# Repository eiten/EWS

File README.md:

# 🔌 Universal Voron Power & CAN HAT (EWS)

> 🌍 **Languages:** [English](README.md) | [Deutsch](README.de.md)

A universal interface board (HAT) for Raspberry Pi 4/5 and Radxa Rock 5B designed for use in Voron 3D printers. Provides powerful 5V supply (8A), CAN-Bus interface (USB-Bridge or Native), and USB hub.

## 📚 Contents

<!-- @import "[TOC]" {cmd="toc" depthFrom=1 depthTo=6 orderedList=false} -->

<!-- code_chunk_output -->

- [🔌 Universal Voron Power & CAN HAT (EWS)](#-universal-voron-power--can-hat-ews)
  - [📚 Contents](#-contents)
  - [🎯 About EWS](#-about-ews)
  - [🚨 Problems Addressed](#-problems-addressed)
  - [✨ Features](#-features)
    - [🔋 Power Supply (24V Input)](#-power-supply-24v-input)
    - [⚡ DC/DC Converter (5V Output)](#-dcdc-converter-5v-output)
    - [🔌 Logic Power Supply (Power Path)](#-logic-power-supply-power-path)
    - [💻 MCU & CAN Interface](#-mcu--can-interface)
    - [📡 USB Hub](#-usb-hub)
  - [📋 Klipper Configuration](#-klipper-configuration)
    - [Basic MCU Setup](#basic-mcu-setup)
  - [🔌 Pinout & Connector Assignment](#-pinout--connector-assignment)
    - [Power Input](#power-input)
    - [CAN-Bus Ports](#can-bus-ports)
    - [USB Ports](#usb-ports)
  - [🛠️ PCB Specifications](#️-pcb-specifications)
  - [⚠️ Manufacturing Recommendations](#️-manufacturing-recommendations)
    - [PCB Manufacturing](#pcb-manufacturing)
    - [Assembly Notes](#assembly-notes)
    - [Component Sourcing](#component-sourcing)
  - [🛠️ Technical Specifications](#️-technical-specifications)
  - [📚 Additional Resources](#-additional-resources)
  - [📝 Changelog](#-changelog)
  - [License](#license)

<!-- /code_chunk_output -->

## 🎯 About EWS

**EWS** stands for "Eierlegende Wollmilchsau" (German for "egg-laying woolly milk pig") - a humorous term for a universal solution that does everything. This HAT lives up to its nickname by combining multiple essential functions for Voron 3D printer control systems in a single, compact board.

The board addresses common pain points in Voron builds by providing robust power distribution, reliable CAN communication, and convenient USB connectivity while maintaining compatibility with both Raspberry Pi and Radxa Rock 5B single-board computers.

## 🚨 Problems Addressed

This board was designed to solve multiple critical issues commonly encountered in high-performance 3D printer setups:

### ⚡ **Power & Supply Issues**
- **Unstable SBC power supply** - Many setups suffer from voltage drops and power instability
- **Separate power injection required** - USB-C touchscreens often need additional power supplies
- **Power distribution complexity** - Multiple power sources create wiring challenges

### 🔗 **CAN Communication Problems**
- **USB-CAN adapters** - Difficult to mount, unreliable connections, additional failure points
- **Controller board limitations** - Using Spider/Octopus as CAN bridge often has built-in termination resistors
- **CAN topology conflicts** - Can't run both CAN toolheads and ADXL boards simultaneously on many controller boards
- **Native CAN unavailable** - Most SBC setups lack proper native CAN interface utilization

### 🔥 **Safety Concerns**
- **Fire hazard from thermal runaway** - No way to disconnect toolhead power during emergencies
- **Uncontrolled power delivery** - Toolheads remain powered even during faults
- **Limited emergency shutdown** - Difficult to implement comprehensive safety cutoffs

### 🔌 **Wiring & Installation**
- **Complex cable management** - CAN and 24V power start from different locations
- **Multiple connection points** - Increases failure modes and installation complexity
- **Inadequate connector standards** - Mix of different connector types creates confusion

### 🖥️ **USB & Peripheral Issues**
- **Limited USB ports** - SBCs often lack sufficient high-power USB connectivity
- **USB hub limitations** - External hubs add complexity and potential points of failure
- **Power delivery standards** - Inconsistent USB-C power delivery for modern touchscreens

## ✨ Features

### 🔋 Power Supply (24V Input)

- **Input Voltage:** 24V DC nominal
- **Connectors:** XT30PW-F (horizontal) or 5.08mm screw terminal
- **Toolhead Switching:** 2x P-Channel MOSFETs (CJAC70P06, -60V, -70A, RDSon ~8mΩ) controlled by PB2 and PA5 for toolhead power switching (safety feature if PWM-FET on toolhead fails)
- **Overvoltage Protection:** TVS diode (SMAJ26A, 26V Standoff, Unidirectional) to GND
- **Input Protection:** Distributed fusing (5A for DC/DC, 5A each for CAN ports)

### ⚡ DC/DC Converter (5V Output)

- **Controller:** MaxLinear XR76208 (Synchronous Step-Down, 8A, COT)
- **Input Voltage:** 12-24V DC (enable circuit with Zener diode)
- **Input Fuse:** 5A SMD 1812 Slow Blow
- **Reverse Polarity Protection:** SS56 Schottky diode
- **Output Voltage:** 5.1V (set via feedback divider: R_Top=15kΩ, R_Bottom=2.0kΩ)
- **Switching Frequency:** ~600kHz (set via Ron=30kOhm)
- **Inductance:** 3.3µH Shielded (Sunlord MDA1050-3R3M, Isat ~17A)
- **Input Capacitors:** 4x 10µF 1206 ceramic + 1x 100µF electrolytic/polymer (bulk)
- **Output Capacitors:** 4x 22µF 1206 ceramic
- **Stability:** Feed-forward capacitor (Cff) 1nF parallel to upper feedback resistor
- **Soft-Start:** 100nF at SS pin (~6ms startup time)
- **Current Limit:** 5.1kΩ resistor (~10.2A limit)
- **Enable:** Zener diode-based circuit for 12-24V input voltage range

### 🔌 Logic Power Supply (Power Path)

- **Concept:** Separation of +5V_PWR (high current for screen/webcam) and +5V_LOGIC (for MCU/Hub)
- **Diode OR-ing:** 2x Schottky diodes (1N5819WS, 1A)
  - Source 1: USB_VBUS (from Pi/PC) → Diode → +5V_LOGIC
  - Source 2: +5V_BUCK (from 8A regulator) → Diode → +5V_LOGIC
- **Purpose:** Board is USB-flashable without 24V supply, no backflow to PC
- **3.3V Generation:** LDO (XC6206) powered from +5V_LOGIC

### 🧠 MCU & CAN Interface

- **Microcontroller:** STM32G0B1KBU6 (UFQFPN-32)
- **Clocking:** Crystal-less (Internal HSI48 with Clock Recovery System CRS via USB)
- **Pi Connection:**
  - USB (PA11/PA12) to USB Hub
  - UART (PA9/PA10) to Pi Header (Pin 8/10) via jumperable connection
  - NRST to Pi GPIO 22 (via 1kΩ) + button to GND + 100nF cap
  - BOOT0 (Pin 24/PA14 shared with SWCLK) to Pi GPIO 27 (via 1kΩ) + button to 3.3V + 10kΩ pull-down
- **CAN Transceiver:** MCP2542WFD (or compatible)
- **Muxing:** Jumper selectable between STM32 (USB-CAN Bridge) and Rock/Pi Native GPIOs (Pin 3/5). For ROCK 5B/5B+, jumpers can select whether CAN comes from onboard STM32G0B1 or goes natively to Rockchip (via GPIO header Pin 3 (CAN-RX) and Pin 5 (CAN-TX))
- **Termination:** 120 Ω resistor, switchable per jumper (directly at connectors)
- **CAN Connectors:** 2x Molex Micro-Fit 3.0 (2x2)
- **Micro-Fit Pinout:** Pin 1=24V, Pin 2=GND (upper row), Pin 3=CAN_H, Pin 4=CAN_L (lower row)
- **CAN Power Protection:** 5A SMD 1812 Slow Blow per port

### 📡 USB Hub

- **Controller:** WCH CH334F (QFN-24)
- **Speed:** USB 2.0 High Speed (480 Mbit/s) with MTT
- **Clocking:** Internal (crystal-less), XO pin connected to GND for internal oscillator mode
- **Supply:** V5 to +5V_LOGIC
- **Upstream:** To Raspberry Pi Header (USB loopback cable required) or USB-C input
- **Downstream Ports:**
  - STM32 (internal)
  - USB-C connector (for touchscreen)
  - USB-A connector (vertical, for webcam)

**USB Port Protection:**
- **Concept:** 100µF electrolytic tank at +5V_PWR, followed by TPS2557 power distribution switch, followed by 22µF ceramic at connector
- **USB-C Port (Screen):**
  - TPS2557: Power distribution switch with backfeed protection, overcurrent/short-circuit protection
  - Current limiting: Programmable limit via external resistor
  - CC Lines: CC1 and CC2 each with 10kΩ resistor to VBUS (behind switch) for 3A advertisement
  - ESD Protection: SRV05-4 TVS array
- **USB-A Port (Webcam):**
  - TPS2557: Power distribution switch with backfeed protection, overcurrent/short-circuit protection
  - Current limiting: Programmable limit via external resistor
  - ESD Protection: SRV05-4 TVS array

## 📋 Klipper Configuration

### Basic MCU Setup
```ini
[mcu hat]
canbus_uuid: your_uuid_here
# Alternative for USB connection:
# serial: /dev/serial/by-id/usb-katapult_stm32g0b1xx_your_id-if00

[temperature_sensor hat_mcu]
sensor_type: temperature_mcu
sensor_mcu: hat
```

## 🔌 Pinout & Connector Assignment

### Power Input
- **XT30PW-F (horizontal)** or **5.08mm Screw Terminal**
  - Pin 1: +24V
  - Pin 2: GND

### CAN-Bus Ports
- **2x Molex Micro-Fit 3.0 (2x2, THT)**
  - Pin 1: +24V (upper row, left)
  - Pin 2: GND (upper row, right)
  - Pin 3: CAN_H (lower row, left)
  - Pin 4: CAN_L (lower row, right)

### USB Ports
- **USB-C:** Touchscreen connection (5V/3A capability)
- **USB-A:** Webcam connection (vertical mount)

## 🛠️ PCB Specifications

| Parameter | Specification |
|-----------|---------------|
| **Form Factor** | Standard HAT (65mm x 56mm) |
| **Layer Stack** | 4-Layer Multilayer |
| **Layer 1 (Top)** | Signal/Power |
| **Layer 2** | GND Plane |
| **Layer 3** | 5V Power Plane |
| **Layer 4 (Bottom)** | Signal/GND |
| **Solder Mask** | Black Matte |
| **Surface Finish** | ENIG (Gold) |
| **Silkscreen** | White |
| **Mounting** | Inner mounting holes (Pi/Rock compatible) |
| **EMI Design** | Mounting holes via-stitched to GND planes (Layer 2 & Bottom), isolated from 5V plane (Layer 3) |

## ⚠️ Manufacturing Recommendations

### PCB Manufacturing
- **Copper Weight:** **2oz copper recommended** for improved thermal performance and current handling
- **Via Specifications:** Minimum 12-20 vias at DC/DC PGND for thermal management
- **Impedance Control:** 90 Ω differential for USB traces (D+/D- pairs)

### Assembly Notes
- **24V Path:** Minimum 3mm trace width on top & bottom layers for 12A total current
- **5V Distribution:** Use Layer 3 plane with solid connections (no thermals) to headers and capacitors
- **Thermal Management:** QFN GND pads connected with vias, considering bottom layer routing

### Component Sourcing
- Ensure polyfuse derating for chamber temperatures up to 60°C
- Select inductors with sufficient saturation current (>15A recommended)
- Use low-ESR capacitors for switching regulator

## 🛠️ Technical Specifications

| Parameter | Value | Unit |
|-----------|-------|------|
| **Input Voltage** | 24 ± 2 | V |
| **5V Output Current** | 8 | A |
| **Logic Supply Current** | 2 | A |
| **CAN Baud Rate** | up to 1 | Mbit/s |
| **USB Speed** | 480 | Mbit/s |
| **Operating Temperature** | -10 to +70 | °C |
| **Dimensions** | 65 x 56 | mm |

## 📚 Additional Resources

- [Component Datasheets](doc/datasheets/README.md)
- [Klipper Documentation](https://www.klipper3d.org/Config_Reference.html)
- [CAN-Bus Setup Guide](https://www.klipper3d.org/CANBUS.html)
- [Voron Documentation](https://docs.vorondesign.com/)
- [STM32G0 Reference Manual](https://www.st.com/resource/en/reference_manual/rm0454-stm32g0x0-advanced-armbased-32bit-mcus-stmicroelectronics.pdf)
- [Katapult Firmware Flasher](https://github.com/Arksine/katapult)

## 📝 Changelog

For detailed information about changes and updates, see [CHANGELOG.md](CHANGELOG.md).

## License

This project is licensed under the **Creative Commons Attribution-NonCommercial-ShareAlike 4.0 International License** (CC BY-NC-SA 4.0).

This means you are free to:
- **Share** — copy and redistribute the material in any medium or format
- **Adapt** — remix, transform, and build upon the material

Under the following terms:
- **Attribution** — You must give appropriate credit, provide a link to the license, and indicate if changes were made
- **NonCommercial** — You may not use the material for commercial purposes
- **ShareAlike** — If you remix, transform, or build upon the material, you must distribute your contributions under the same license

For the full license text, visit: https://creativecommons.org/licenses/by-nc-sa/4.0/

---

> **Note:** The original documentation is in German ([README.de.md](README.de.md)). This English version is a translation for international users.

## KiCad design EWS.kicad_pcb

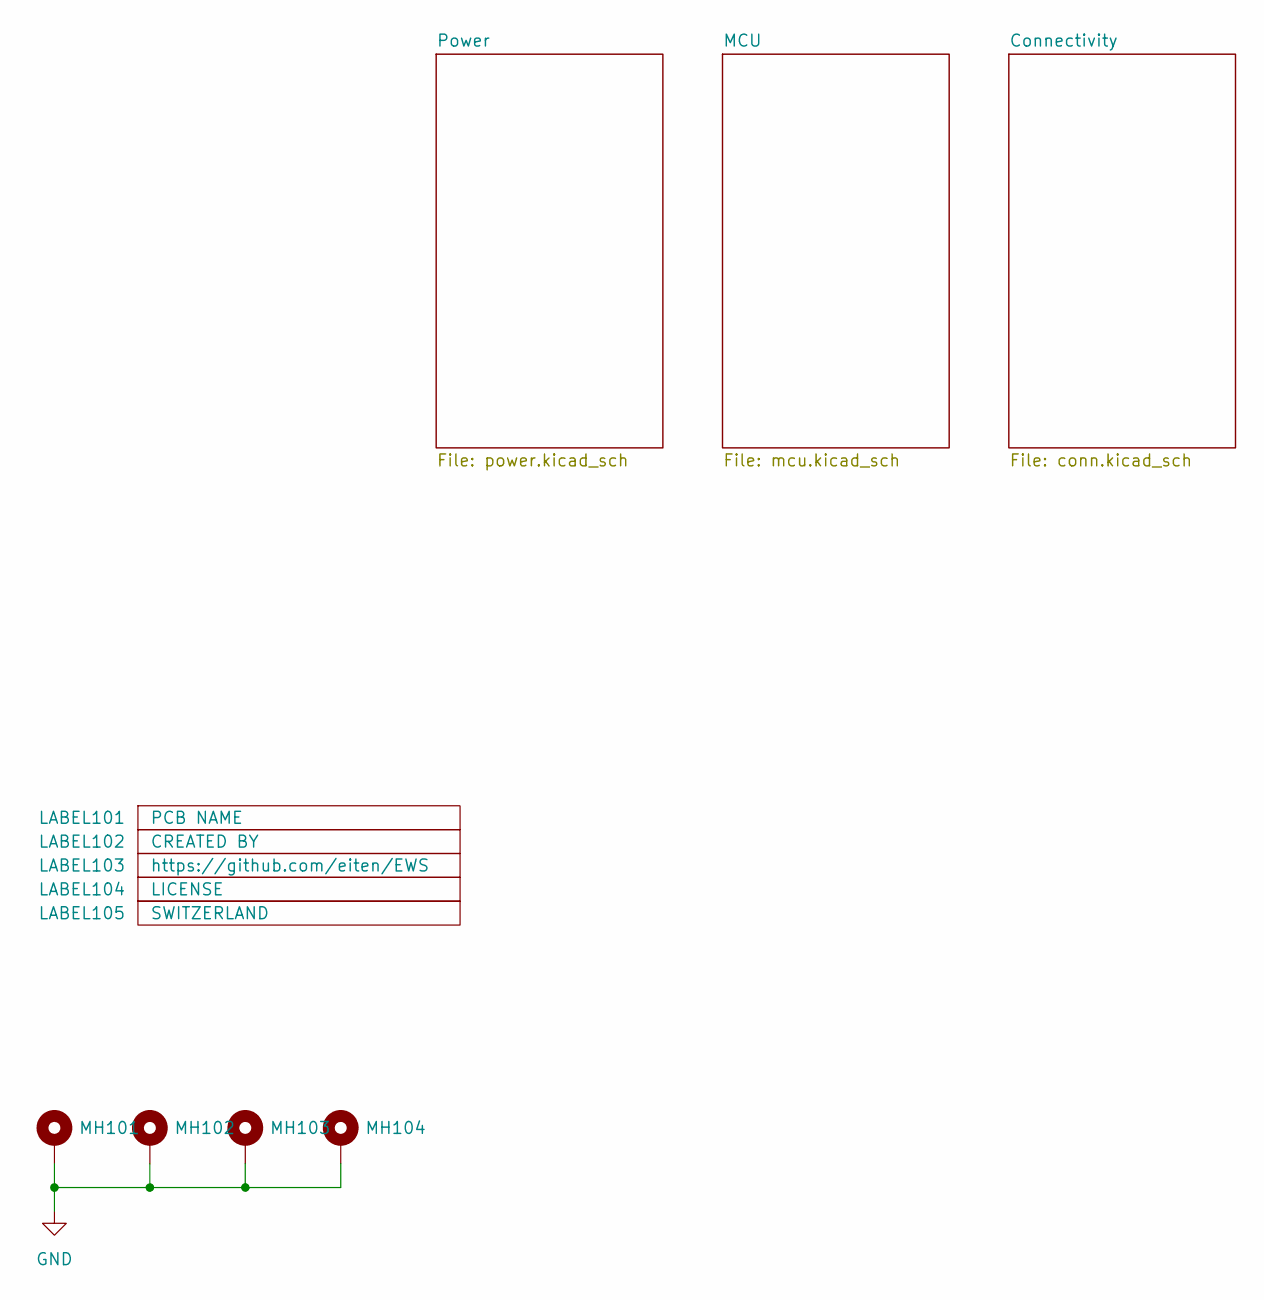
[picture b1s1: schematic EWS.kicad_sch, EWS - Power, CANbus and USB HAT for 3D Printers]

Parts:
LABEL101: PCB NAME; EWS Rev. 1.0
LABEL102: CREATED BY; EduardIten
LABEL103: https://github.com/eiten/EWS; http___github.com_eiten_EWS
LABEL104: LICENSE; CC_BY_NC_SA 4
LABEL105: SWITZERLAND; Switzerland
MH101, MH102, MH103, MH104: MountingHole_Pad; MountingHole_2.7mm_Pad_Via

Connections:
GND: MH101.1, MH102.1, MH103.1, MH104.1; also elsewhere on the board

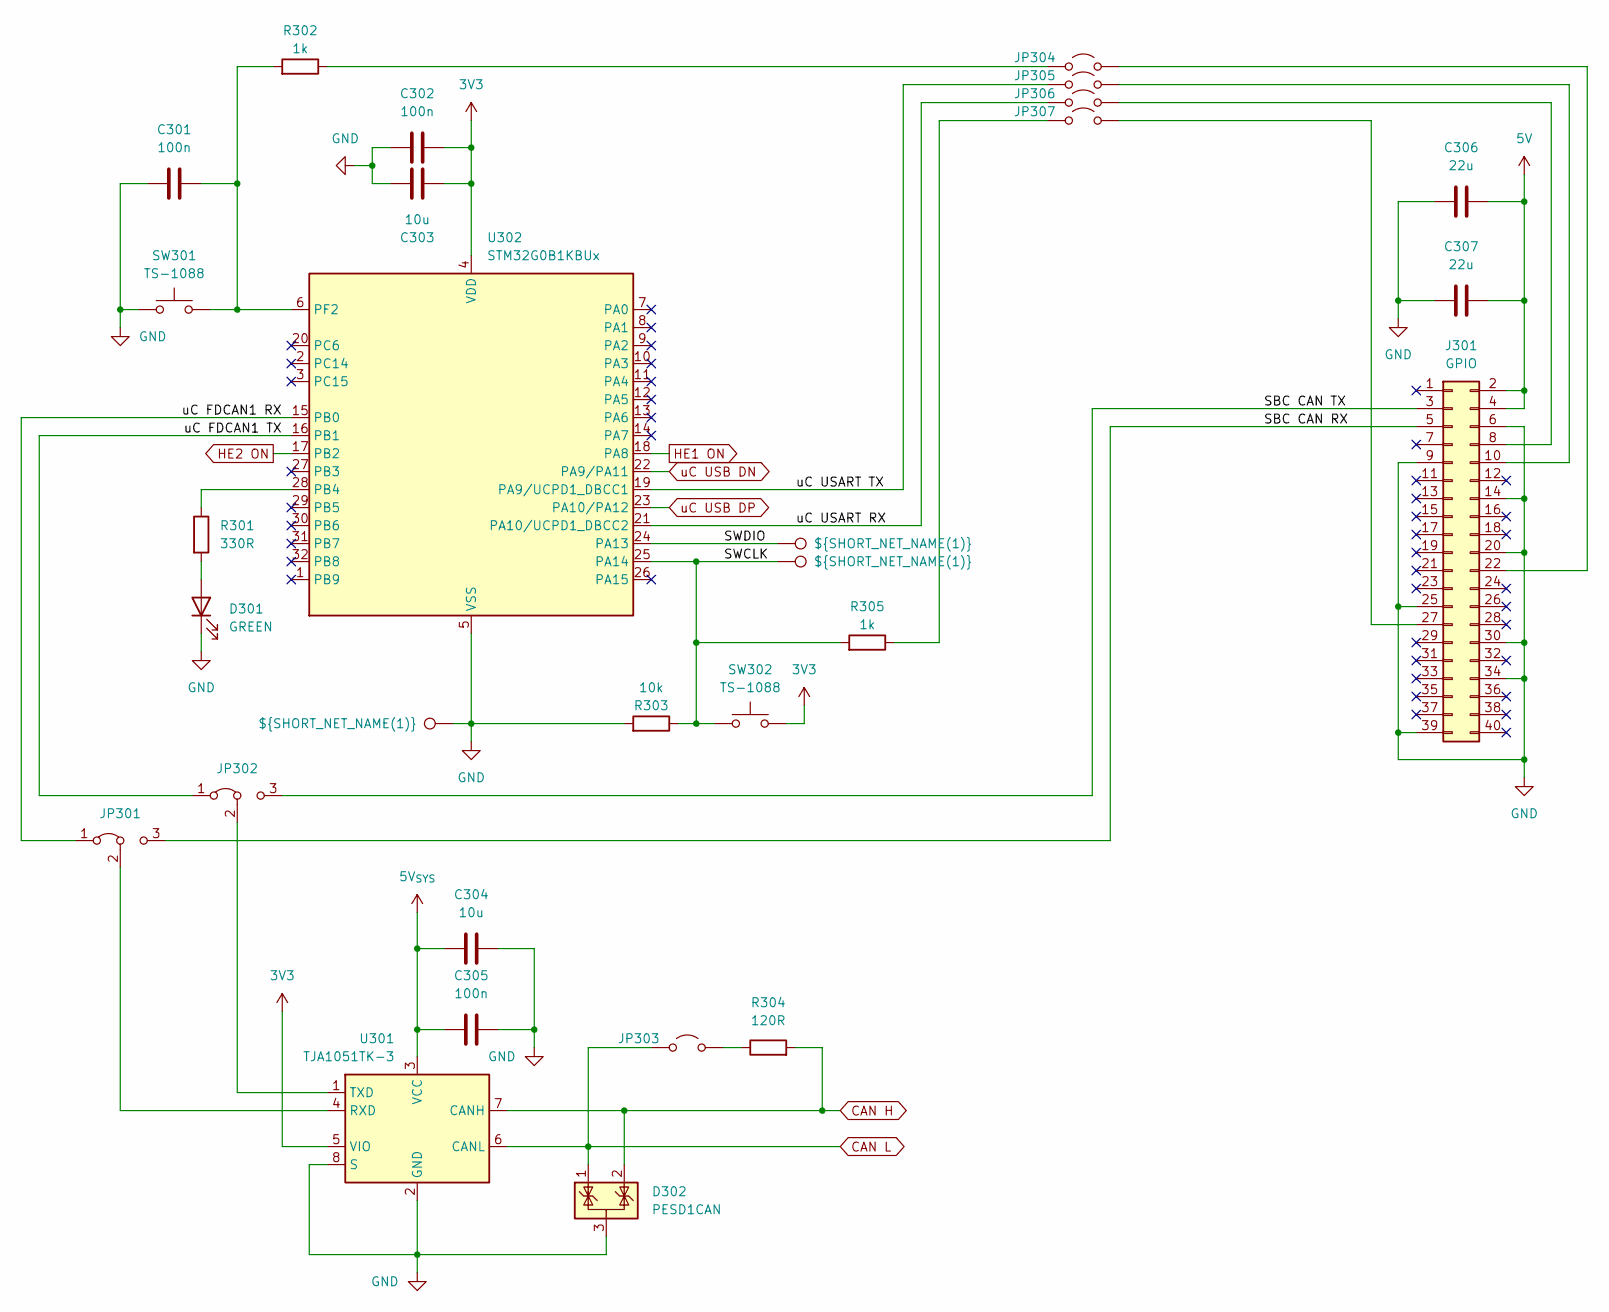
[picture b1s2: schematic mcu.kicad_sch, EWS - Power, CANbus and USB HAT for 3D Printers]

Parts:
C301, C302, C305: 100n; C_0402_1005Metric; Manufacturer Part # CL05B104KB54PNC; LCSC Part # C307331
C303, C304: 10u; C_0603_1608Metric; Manufacturer Part # CL10A106MA8NRNC; LCSC Part # C96446
C306, C307: 22u; C_1206_3216Metric; Manufacturer Part # CL31A226KAHNNNE; LCSC Part # C12891
D301: GREEN; LED_0805_2012Metric; Manufacturer Part # KT-0805G; LCSC Part # C2297
D302: PESD1CAN; SOT-23; Manufacturer Part # PESD1CAN; LCSC Part # C907838
J301: GPIO; PinSocket_2x20_P2.54mm_Vertical
JP301, JP302: SolderJumper-3_P1.3mm_Bridged12_RoundedPad1.0x1.5mm_custom
JP303, JP304, JP305, JP306, JP307: SolderJumper-2_P1.3mm_Open_RoundedPad1.0x1.5mm
R301: 330R; R_0402_1005Metric; Manufacturer Part # 0402WGF3300TCE; LCSC Part # C25104
R302, R305: 1k; R_0402_1005Metric; Manufacturer Part # 0402WGF1001TCE; LCSC Part # C11702
R303: 10k; R_0402_1005Metric; Manufacturer Part # 0402WGF1002TCE; LCSC Part # C25744
R304: 120R; R_0603_1608Metric; Manufacturer Part # 0603WAF1200T5E; LCSC Part # C22787
SW301, SW302: TS-1088; SW_SPST_TS-1088-xR020; Manufacturer Part # TS-1088-AR02016; LCSC Part # C720477
TP301, TP302, TP303: ${SHORT_NET_NAME(1)}; NAMED_TEST_POINT
U301: TJA1051TK-3; HVSON-8-1EP_3x3mm_P0.65mm_EP1.6x2.4mm; Manufacturer Part # TJA1051TK/3/1J; LCSC Part # C2875699
U302: STM32G0B1KBUx; QFN-32-1EP_5x5mm_P0.5mm_EP3.45x3.45mm; Manufacturer Part # STM32G0B1KBU6; LCSC Part # C5159549

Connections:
3V3: C302.2, C303.1, SW302.1, U301.5 (VIO), U302.4 (VDD); also elsewhere on the board
5V: C306.2, C307.2, J301.2, J301.4; also elsewhere on the board
5V_{SYS}: C304.1, C305.2, U301.3 (VCC); also elsewhere on the board
/MCU/SBC CAN RX: J301.5, JP301.3 (B)
/MCU/SBC CAN TX: J301.3, JP302.3 (B)
/MCU/SWCLK: R303.1, R305.2, SW302.2, TP303.1, U302.25 (PA14)
/MCU/SWDIO: TP302.1, U302.24 (PA13)
/MCU/uC FDCAN1 RX: JP301.1 (A), U302.15 (PB0)
/MCU/uC FDCAN1 TX: JP302.1 (A), U302.16 (PB1)
/MCU/uC USART RX: JP306.1 (A), U302.21 (PA10/UCPD1_DBCC2)
/MCU/uC USART TX: JP305.1 (A), U302.19 (PA9/UCPD1_DBCC1)
CAN H: D302.2 (K), R304.2, U301.7 (CANH); also elsewhere on the board
CAN L: D302.1 (K), JP303.1 (A), U301.6 (CANL); also elsewhere on the board
GND: C301.1, C302.1, C303.2, C304.2, C305.1, C306.1, C307.1, D301.1 (K), D302.3 (A), J301.6, J301.9, J301.14, J301.20, J301.25, J301.30, J301.34, J301.39, R303.2, SW301.1, TP301.1, U301.2 (GND), U301.8 (S), U301.9 (GND), U302.5 (VSS), U302.33 (VSS); also elsewhere on the board
HE1 ON: U302.18 (PA8); also elsewhere on the board
HE2 ON: U302.17 (PB2); also elsewhere on the board
unnamed: D301.2 (A), R301.2
unnamed: J301.8, JP306.2 (B)
unnamed: J301.10, JP305.2 (B)
unnamed: J301.22, JP304.2 (B)
unnamed: J301.27, JP307.2 (B)
unnamed: JP301.2 (C), U301.4 (RXD)
unnamed: JP302.2 (C), U301.1 (TXD)
unnamed: JP303.2 (B), R304.1
unnamed: JP304.1 (A), R302.1
unnamed: JP307.1 (A), R305.1
unnamed: R301.1, U302.28 (PB4)
unnamed: C301.2, R302.2, SW301.2, U302.6 (PF2)
uC USB DN: U302.22 (PA9/PA11); also elsewhere on the board
uC USB DP: U302.23 (PA10/PA12); also elsewhere on the board

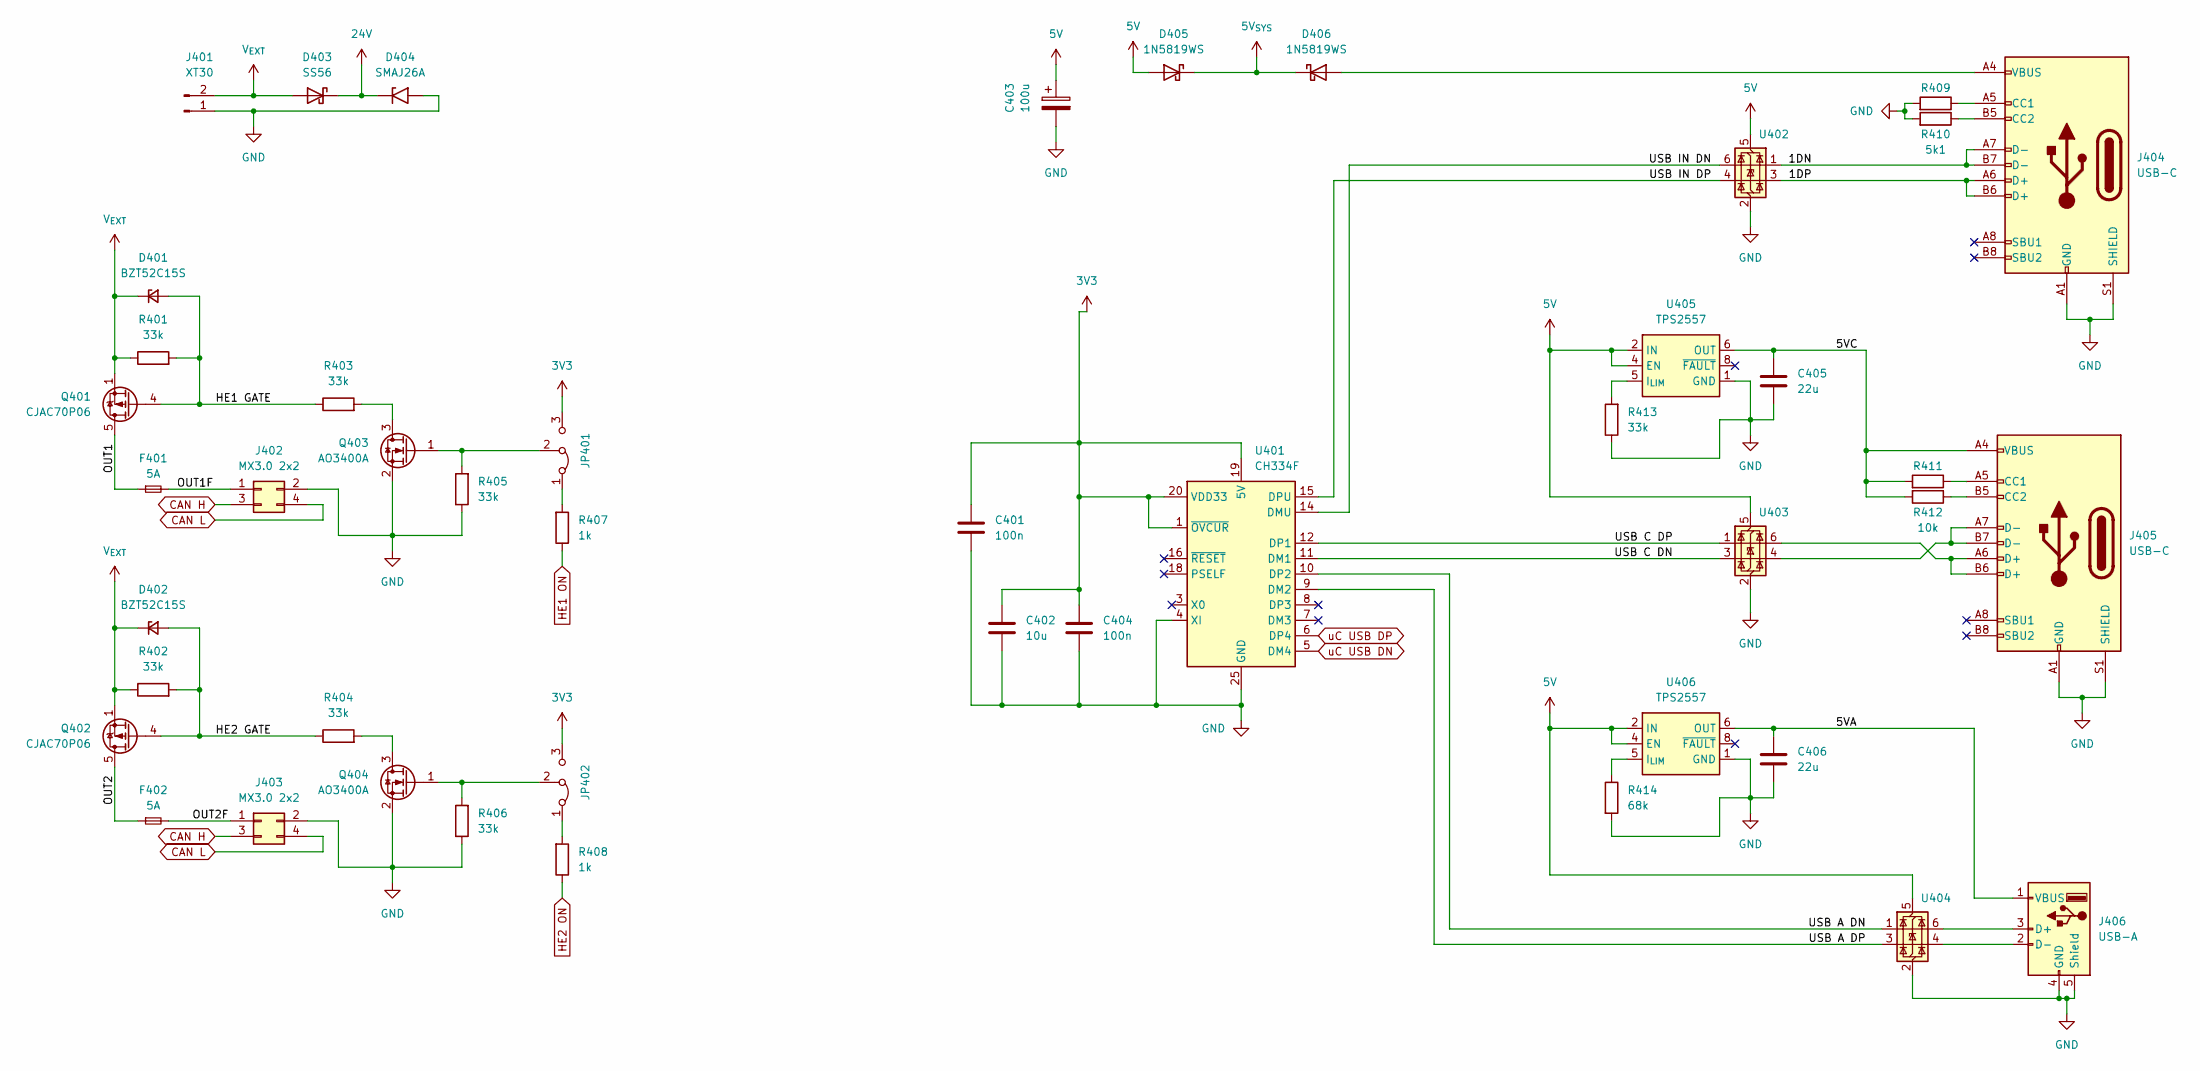
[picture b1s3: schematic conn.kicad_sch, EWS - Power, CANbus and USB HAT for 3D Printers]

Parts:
C401, C404: 100n; C_0402_1005Metric; Manufacturer Part # CL05B104KB54PNC; LCSC Part # C307331
C402: 10u; C_0603_1608Metric; Manufacturer Part # CL10A106MA8NRNC; LCSC Part # C96446
C403: 100u; CP_Elec_6.3x7.7; Manufacturer Part # RVT1H101M0607; LCSC Part # C3151829
C405, C406: 22u; C_1206_3216Metric; Manufacturer Part # CL31A226KAHNNNE; LCSC Part # C12891
D401, D402: BZT52C15S; D_SOD-323; Manufacturer Part # BZT52C15S; LCSC Part # C19077448
D403: SS56; D_SMC; Manufacturer Part # SS56C; LCSC Part # C24138
D404: SMAJ26A; D_SMA; Manufacturer Part # SMAJ26A; LCSC Part # C19077543
D405, D406: 1N5819WS; D_SOD-323; Manufacturer Part # 1N5819WS; LCSC Part # C191023
F401, F402: 5A; Fuse_1206_3216Metric_Pad1.42x1.75mm_HandSolder; Manufacturer Part # CFS12V3T5R0; LCSC Part # C163128
J401: XT30; AMASS_XT30PW-M_1x02_P2.50mm_Horizontal; Manufacturer Part # XT30PW-M30.G.Y; LCSC Part # C431092
J402, J403: MX3.0 2x2; Molex_Micro-Fit_3.0_43045-0400_2x02_P3.00mm_Horizontal; Manufacturer Part # 430450400; LCSC Part # C122413
J404, J405: USB-C; USB_C_Receptacle_GCT_USB4105-xx-A_16P_TopMnt_Horizontal; Manufacturer Part # TYPE-C 16PIN 2MD(073); LCSC Part # C2765186
J406: USB-A; USB_A_Wuerth_614004134726_Horizontal; Manufacturer Part # BX-TYPE-A-MCC4P; LCSC Part # C18077685
JP401, JP402: SolderJumper-3_P1.3mm_Bridged12_RoundedPad1.0x1.5mm_custom
Q401, Q402: CJAC70P06; AO_DFN-8-1EP_5.55x5.2mm_P1.27mm_EP4.12x4.6mm; Manufacturer Part # CJAC70P06; LCSC Part # C2898279
Q403, Q404: AO3400A; SOT-23; Manufacturer Part # AO3400A; LCSC Part # C20917
R401, R402, R403, R404, R405, R406, R413: 33k; R_0402_1005Metric; Manufacturer Part # 0402WGF3302TCE; LCSC Part # C25779
R407, R408: 1k; R_0402_1005Metric; Manufacturer Part # 0402WGF1001TCE; LCSC Part # C11702
R409, R410: 5k1; R_0402_1005Metric; Manufacturer Part # 0402WGF5101TCE; LCSC Part # C25905
R411, R412: 10k; R_0402_1005Metric; Manufacturer Part # 0402WGF1002TCE; LCSC Part # C25744
R414: 68k; R_0603_1608Metric; Manufacturer Part # 0603WAF6802T5E; LCSC Part # C23231
U401: CH334F; QFN-24-1EP_4x4mm_P0.5mm_EP2.7x2.7mm_ThermalVias; Manufacturer Part # CH334F; LCSC Part # C5187527
U402, U403, U404: USBLC6-2SC6; SOT-23-6; Manufacturer Part # USBLC6-2SC6; LCSC Part # C2687116
U405, U406: TPS2557; S-PVSON-N8

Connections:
3V3: C401.1, C402.1, C404.1, JP401.3 (B), JP402.3 (B), U401.1 (~OVCUR), U401.19 (5V), U401.20 (VDD33); also elsewhere on the board
5V: C403.1, D405.2 (A), U402.5 (VBUS), U403.5 (VBUS), U404.5 (VBUS), U405.2 (IN), U405.3 (IN), U405.4 (EN), U406.2 (IN), U406.3 (IN), U406.4 (EN); also elsewhere on the board
5V_{SYS}: D405.1 (K), D406.1 (K); also elsewhere on the board
24V: D403.1 (K), D404.1 (A1); also elsewhere on the board
/Connectivity/1DN: J404.A7 (D-), J404.B7 (D-), U402.1 (I/O1)
/Connectivity/1DP: J404.A6 (D+), J404.B6 (D+), U402.3 (I/O2)
/Connectivity/5VA: C406.1, J406.1 (VBUS), U406.6 (OUT), U406.7 (OUT)
/Connectivity/5VC: C405.1, J405.A4 (VBUS), J405.A9 (VBUS), J405.B4 (VBUS), J405.B9 (VBUS), R411.2, R412.2, U405.6 (OUT), U405.7 (OUT)
/Connectivity/HE1 GATE: D401.2 (A), Q401.4 (G), R401.2, R403.1
/Connectivity/HE2 GATE: D402.2 (A), Q402.4 (G), R402.2, R404.1
/Connectivity/OUT1: F401.1, Q401.5 (D)
/Connectivity/OUT1F: F401.2, J402.1
/Connectivity/OUT2: F402.1, Q402.5 (D)
/Connectivity/OUT2F: F402.2, J403.1
/Connectivity/USB A DN: U401.10 (DP2), U404.1 (I/O1)
/Connectivity/USB A DP: U401.9 (DM2), U404.3 (I/O2)
/Connectivity/USB C DN: U401.11 (DM1), U403.3 (I/O2)
/Connectivity/USB C DP: U401.12 (DP1), U403.1 (I/O1)
/Connectivity/USB IN DN: U401.14 (DMU), U402.6 (I/O1)
/Connectivity/USB IN DP: U401.15 (DPU), U402.4 (I/O2)
CAN H: J402.3, J403.3; also elsewhere on the board
CAN L: J402.4, J403.4; also elsewhere on the board
GND: C401.2, C402.2, C403.2, C404.2, C405.2, C406.2, D404.2 (A2), J401.1, J402.2, J403.2, J404.A1 (GND), J404.A12 (GND), J404.B1 (GND), J404.B12 (GND), J404.S1 (SHIELD), J405.A1 (GND), J405.A12 (GND), J405.B1 (GND), J405.B12 (GND), J405.S1 (SHIELD), J406.4 (GND), J406.5 (Shield), Q403.2 (S), Q404.2 (S), R405.1, R406.1, R409.2, R410.2, R413.1, R414.2, U401.4 (XI), U401.25 (GND), U402.2 (GND), U403.2 (GND), U404.2 (GND), U405.1 (GND), U405.9 (GND), U406.1 (GND), U406.9 (GND); also elsewhere on the board
HE1 ON: R407.1; also elsewhere on the board
HE2 ON: R408.1; also elsewhere on the board
unnamed: D406.2 (A), J404.A4 (VBUS), J404.A9 (VBUS), J404.B4 (VBUS), J404.B9 (VBUS)
unnamed: J404.A5 (CC1), R409.1
unnamed: J404.B5 (CC2), R410.1
unnamed: J405.A5 (CC1), R411.1
unnamed: J405.B5 (CC2), R412.1
unnamed: J405.A6 (D+), J405.B6 (D+), U403.6 (I/O1)
unnamed: J405.A7 (D-), J405.B7 (D-), U403.4 (I/O2)
unnamed: J406.3 (D+), U404.6 (I/O1)
unnamed: J406.2 (D-), U404.4 (I/O2)
unnamed: JP401.1 (A), R407.2
unnamed: JP401.2 (C), Q403.1 (G), R405.2
unnamed: JP402.1 (A), R408.2
unnamed: JP402.2 (C), Q404.1 (G), R406.2
unnamed: Q403.3 (D), R403.2
unnamed: Q404.3 (D), R404.2
unnamed: R413.2, U405.5 (I_{LIM})
unnamed: R414.1, U406.5 (I_{LIM})
V_{EXT}: D401.1 (K), D402.1 (K), D403.2 (A), J401.2, Q401.1 (S), Q401.2 (S), Q401.3 (S), Q402.1 (S), Q402.2 (S), Q402.3 (S), R401.1, R402.1
uC USB DN: U401.5 (DM4); also elsewhere on the board
uC USB DP: U401.6 (DP4); also elsewhere on the board

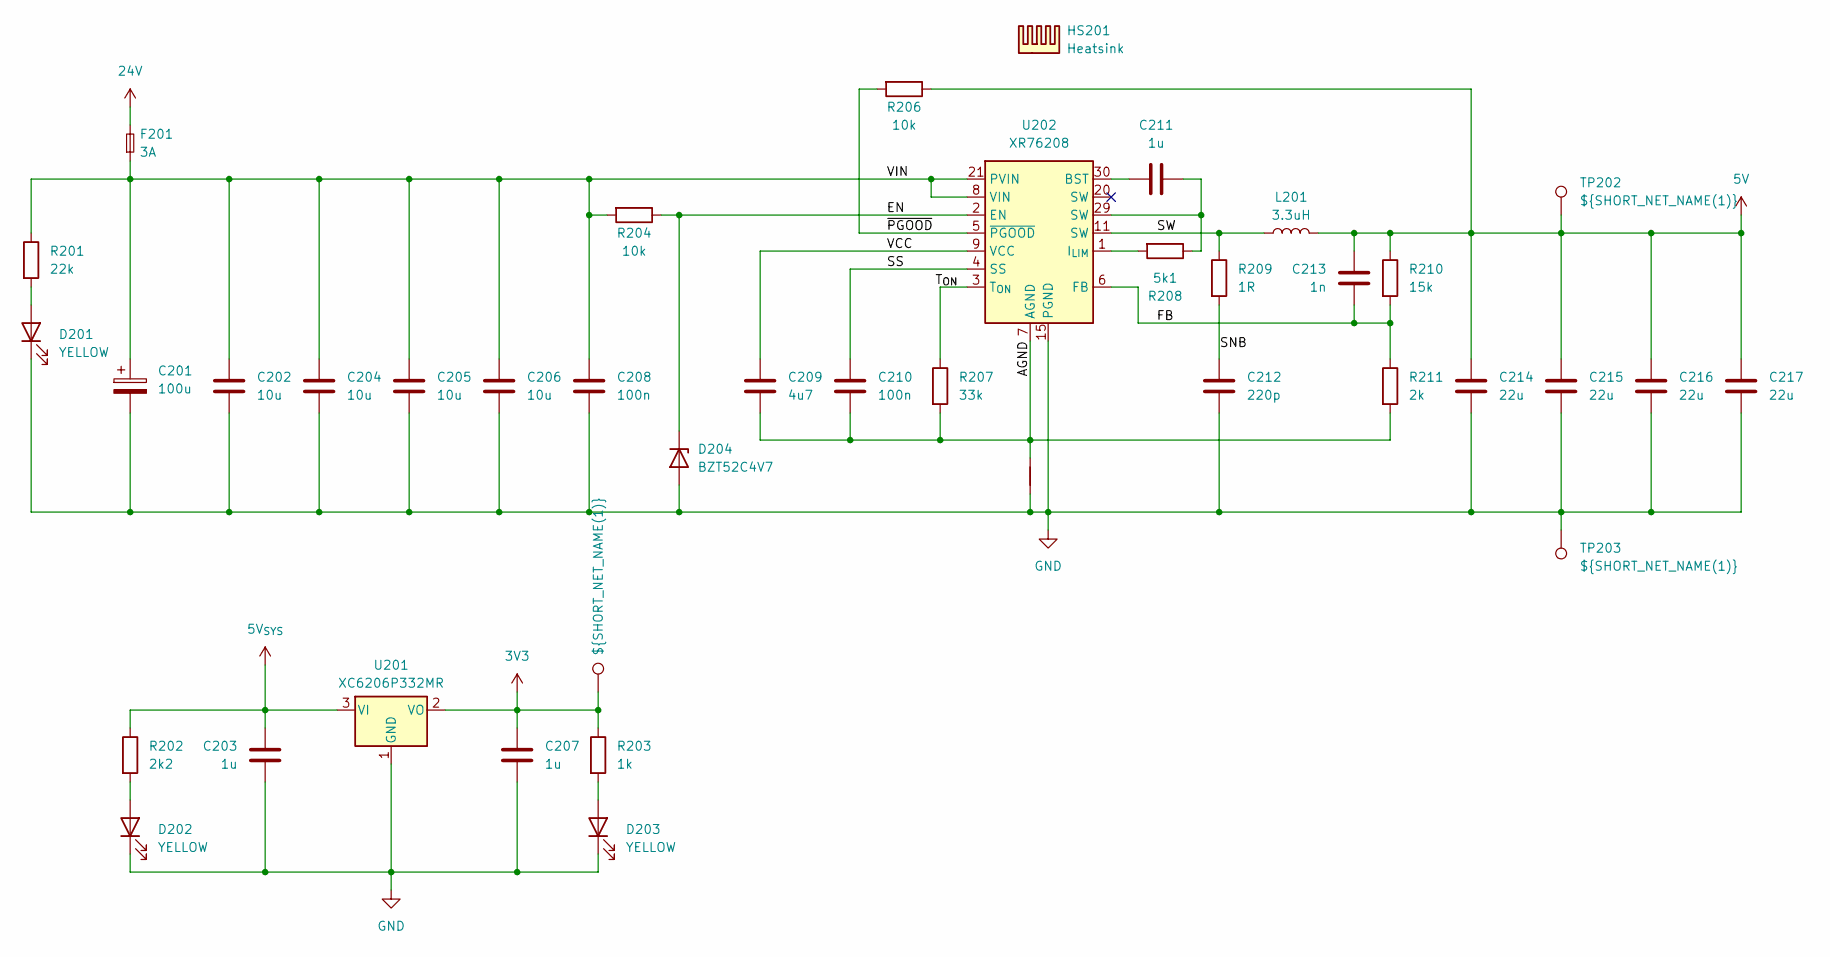
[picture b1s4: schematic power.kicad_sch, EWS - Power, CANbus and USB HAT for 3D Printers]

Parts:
C201: 100u; CP_Elec_6.3x7.7; Manufacturer Part # RVT1H101M0607; LCSC Part # C3151829
C202, C204, C205, C206: 10u; C_1206_3216Metric; Manufacturer Part # CL31A106KBHNNNE; LCSC Part # C13585
C203, C207, C211: 1u; C_0402_1005Metric; Manufacturer Part # CL05A105KA5NQNC; LCSC Part # C52923
C208, C210: 100n; C_0402_1005Metric; Manufacturer Part # CL05B104KB54PNC; LCSC Part # C307331
C209: 4u7; C_0402_1005Metric; Manufacturer Part # CL05A475MP5NRNC; LCSC Part # C23733
C212: 220p; C_0603_1608Metric; Manufacturer Part # CL10B221KB8NNNC; LCSC Part # C1603
C213: 1n; C_0402_1005Metric; Manufacturer Part # 0402B102K500NT; LCSC Part # C1523
C214, C215, C216, C217: 22u; C_1206_3216Metric; Manufacturer Part # CL31A226KAHNNNE; LCSC Part # C12891
D201, D202, D203: YELLOW; LED_0805_2012Metric; Manufacturer Part # KT-0805Y; LCSC Part # C2296
D204: BZT52C4V7; D_SOD-123; Manufacturer Part # BZT52C4V7; LCSC Part # C19077400
F201: 3A; Fuse_1206_3216Metric_Pad1.42x1.75mm_HandSolder; Manufacturer Part # CFS12V3T3R00; LCSC Part # C163126
HS201: Heatsink; HeatSink_9x9x5
L201: 3.3uH; L_APV_APH1050; Manufacturer Part # MDA1050-3R3M; LCSC Part # C2847560
NT201: NetTie_2; NetTie-2_SMD_Pad0.5mm
R201: 22k; R_0402_1005Metric; Manufacturer Part # 0402WGF2202TCE; LCSC Part # C25768
R202: 2k2; R_0402_1005Metric; Manufacturer Part # 0402WGF2201TCE; LCSC Part # C25879
R203: 1k; R_0402_1005Metric; Manufacturer Part # 0402WGF1001TCE; LCSC Part # C11702
R204, R206: 10k; R_0402_1005Metric; Manufacturer Part # 0402WGF1002TCE; LCSC Part # C25744
R207: 33k; R_0402_1005Metric; Manufacturer Part # 0402WGF3302TCE; LCSC Part # C25779
R208: 5k1; R_0402_1005Metric; Manufacturer Part # 0402WGF5101TCE; LCSC Part # C25905
R209: 1R; R_0603_1608Metric; Manufacturer Part # 0603WAF100KT5E; LCSC Part # C22936
R210: 15k; R_0402_1005Metric; Manufacturer Part # 0402WGF1502TCE; LCSC Part # C25756
R211: 2k; R_0402_1005Metric; Manufacturer Part # 0402WGF2001TCE; LCSC Part # C4109
TP201: ${SHORT_NET_NAME(1)}; NAMED_TEST_POINT
TP202, TP203: ${SHORT_NET_NAME(1)}; TestPoint_Pad_D3.0mm
U201: XC6206P332MR; SOT-23-3; Manufacturer Part # XC6206P332MR-G; LCSC Part # C5446
U202: XR76208; IC_XR76208ELTR-F; Manufacturer Part # XR76208ELTR-F; LCSC Part # C555356

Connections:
3V3: C207.2, R203.1, TP201.1, U201.2 (VO); also elsewhere on the board
5V: C213.1, C214.1, C215.1, C216.1, C217.1, L201.2, R206.1, R210.1, TP202.1; also elsewhere on the board
5V_{SYS}: C203.2, R202.1, U201.3 (VI); also elsewhere on the board
24V: F201.2; also elsewhere on the board
/Power/AGND: C209.2, C210.2, NT201.2, R207.2, R211.2, U202.7 (AGND), U202.10 (AGND)
/Power/EN: D204.1 (K), R204.1, U202.2 (EN)
/Power/FB: C213.2, R210.2, R211.1, U202.6 (FB)
/Power/SNB: C212.1, R209.2
/Power/SS: C210.1, U202.4 (SS)
/Power/SW: L201.1, R209.1, U202.11 (SW), U202.12 (SW), U202.13 (SW), U202.14 (SW)
/Power/T_{ON}: R207.1, U202.3 (T_{ON})
/Power/VCC: C209.1, U202.9 (VCC)
/Power/VIN: C201.1, C202.1, C204.1, C205.1, C206.1, C208.1, F201.1, R201.1, R204.2, U202.8 (VIN), U202.21 (PVIN), U202.22 (PVIN), U202.23 (PVIN), U202.24 (PVIN), U202.25 (PVIN), U202.26 (PVIN), U202.27 (PVIN), U202.28 (PVIN)
/Power/~PGOOD: R206.2, U202.5 (~PGOOD)
GND: C201.2, C202.2, C203.1, C204.2, C205.2, C206.2, C207.1, C208.2, C212.2, C214.2, C215.2, C216.2, C217.2, D201.1 (K), D202.1 (K), D203.1 (K), D204.2 (A), NT201.1, TP203.1, U201.1 (GND), U202.15 (PGND), U202.16 (PGND), U202.17 (PGND), U202.18 (PGND), U202.19 (PGND); also elsewhere on the board
unnamed: C211.2, R208.1, U202.29 (SW)
unnamed: D201.2 (A), R201.2
unnamed: D202.2 (A), R202.2
unnamed: D203.2 (A), R203.2
unnamed: C211.1, U202.30 (BST)
unnamed: R208.2, U202.1 (I_{LIM})

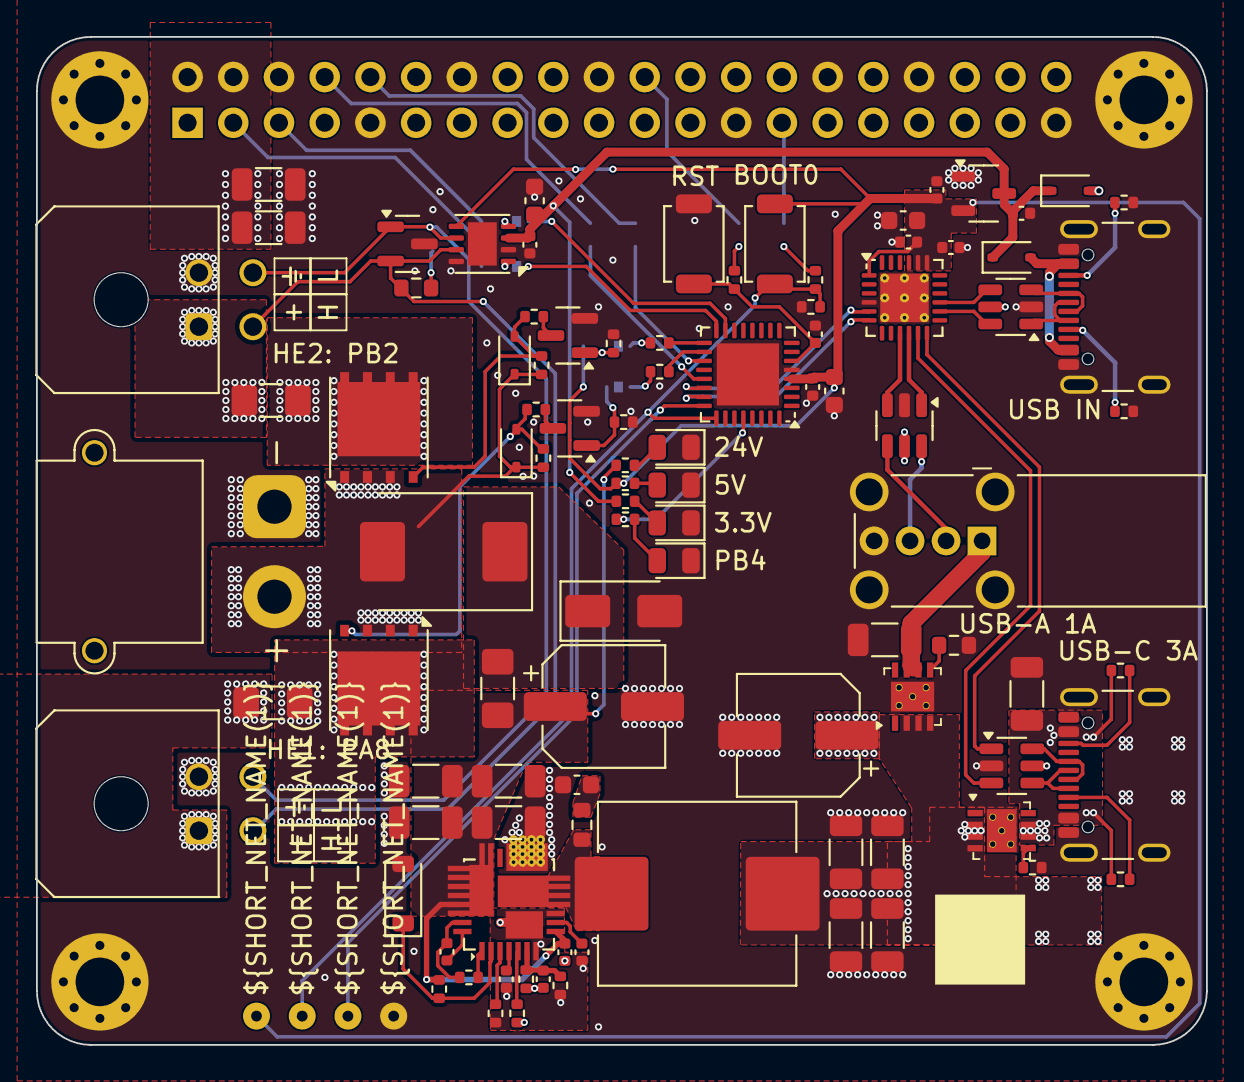
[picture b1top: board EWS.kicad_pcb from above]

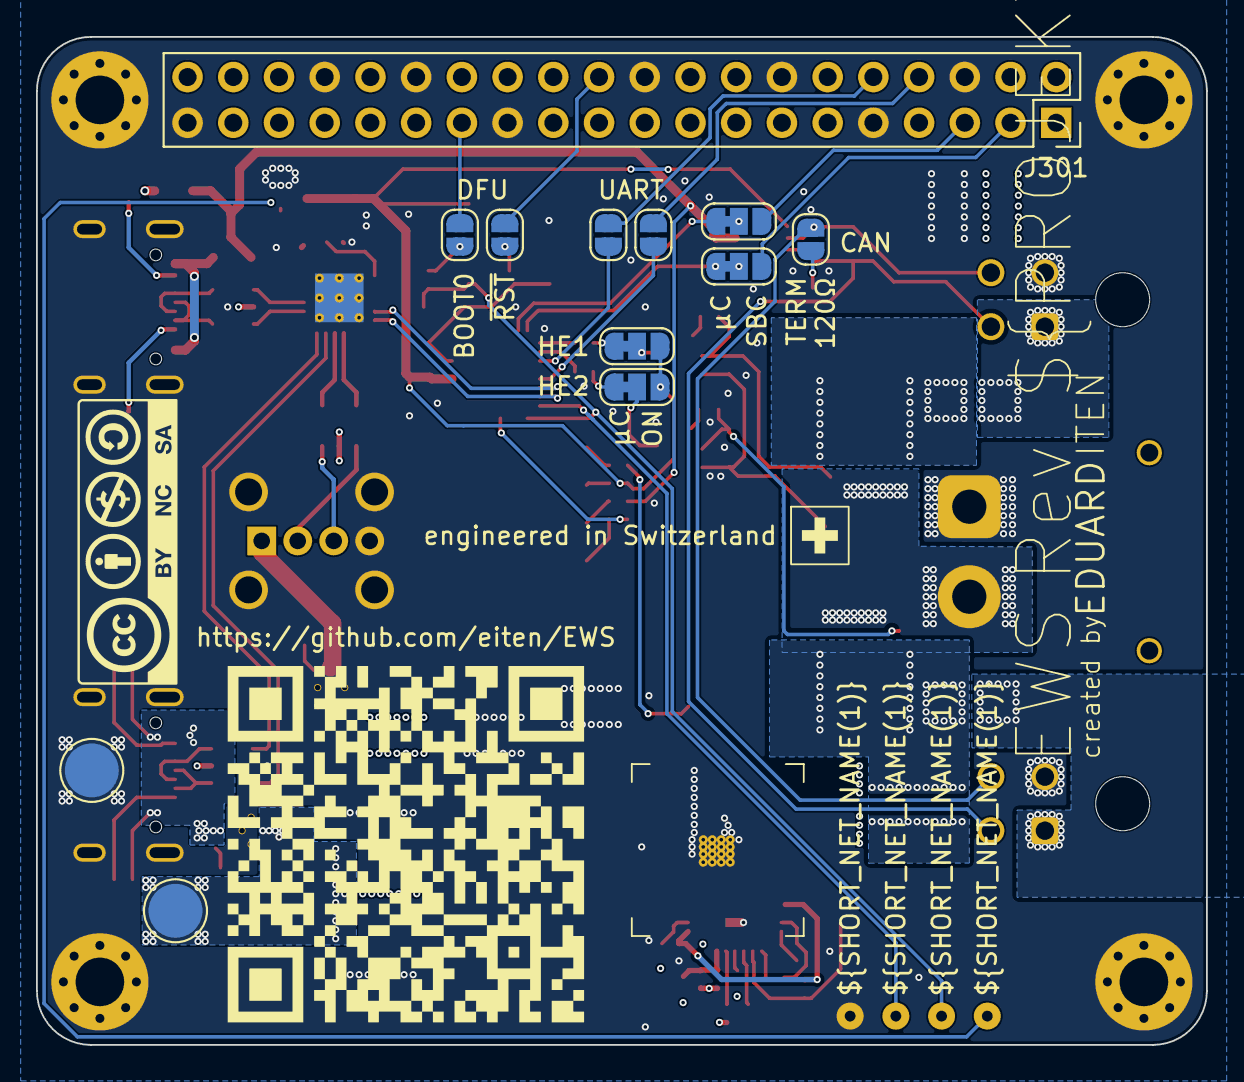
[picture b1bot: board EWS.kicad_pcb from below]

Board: 4 copper layers, 65.0 x 56.0 mm, 124 parts (18 on the bottom side), 81 nets.

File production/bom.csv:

Designator,Footprint,Quantity,Value,LCSC Part #
"C201, C403",CP_Elec_6.3x7.7,2,100u,C3151829
"C202, C204, C205, C206",1206,4,10u,C13585
"C203, C207, C211",0402,3,1u,C52923
"C208, C210, C301, C302, C305, C401, C404",0402,7,100n,C307331
C209,0402,1,4u7,C23733
C212,0603,1,220p,C1603
C213,0402,1,1n,C1523
"C214, C215, C216, C217, C306, C307, C405, C406",1206,8,22u,C12891
"C303, C304, C402",0603,3,10u,C96446
"D201, D202, D203",0805,3,YELLOW,C2296
D204,D_SOD-123,1,BZT52C4V7,C19077400
D301,0805,1,GREEN,C2297
D302,SOT-23,1,PESD1CAN,C907838
"D401, D402",D_SOD-323,2,BZT52C15S,C19077448
D403,D_SMC,1,SS56,C24138
D404,D_SMA,1,SMAJ26A,C19077543
"D405, D406",D_SOD-323,2,1N5819WS,C191023
F201,1206,1,3A,C163126
"F401, F402",1206,2,5A,C163128
HS201,HeatSink_9x9x5,1,Heatsink,
J301,PinSocket_2x20_P2.54mm_Vertical,1,GPIO,
J401,AMASS_XT30PW-M_1x02_P2.50mm_Horizontal,1,XT30,C431092
"J402, J403",Molex_Micro-Fit_3.0_43045-0400_2x02_P3.00mm_Horizontal,2,MX3.0 2x2,C122413
"J404, J405",USB_C_Receptacle_GCT_USB4105-xx-A_16P_TopMnt_Horizontal,2,USB-C,C2765186
J406,USB_A_Wuerth_614004134726_Horizontal,1,USB-A,C18077685
L201,L_APV_APH1050,1,3.3uH,C2847560
"Q401, Q402",AO_DFN-8-1EP_5.55x5.2mm_P1.27mm_EP4.12x4.6mm,2,CJAC70P06,C2898279
"Q403, Q404",SOT-23,2,AO3400A,C20917
R201,0402,1,22k,C25768
R202,0402,1,2k2,C25879
"R203, R302, R305, R407, R408",0402,5,1k,C11702
"R204, R206, R303, R411, R412",0402,5,10k,C25744
"R207, R401, R402, R403, R404, R405, R406, R413",0402,8,33k,C25779
"R208, R409, R410",0402,3,5k1,C25905
R209,0603,1,1R,C22936
R210,0402,1,15k,C25756
R211,0402,1,2k,C4109
R301,0402,1,330R,C25104
R304,0603,1,120R,C22787
R414,0603,1,68k,C23231
"SW301, SW302",SW_SPST_TS-1088-xR020,2,TS-1088,C720477
U201,SOT-23-3,1,XC6206P332MR,C5446
U202,IC_XR76208ELTR-F,1,XR76208,C555356
U301,HVSON-8-1EP_3x3mm_P0.65mm_EP1.6x2.4mm,1,TJA1051TK-3,C2875699
U302,QFN-32-1EP_5x5mm_P0.5mm_EP3.45x3.45mm,1,STM32G0B1KBUx,C5159549
U401,QFN-24-1EP_4x4mm_P0.5mm_EP2.7x2.7mm_ThermalVias,1,CH334F,C5187527
"U402, U403, U404",SOT-23-6,3,USBLC6-2SC6,C2687116
"U405, U406",S-PVSON-N8,2,TPS2557,
